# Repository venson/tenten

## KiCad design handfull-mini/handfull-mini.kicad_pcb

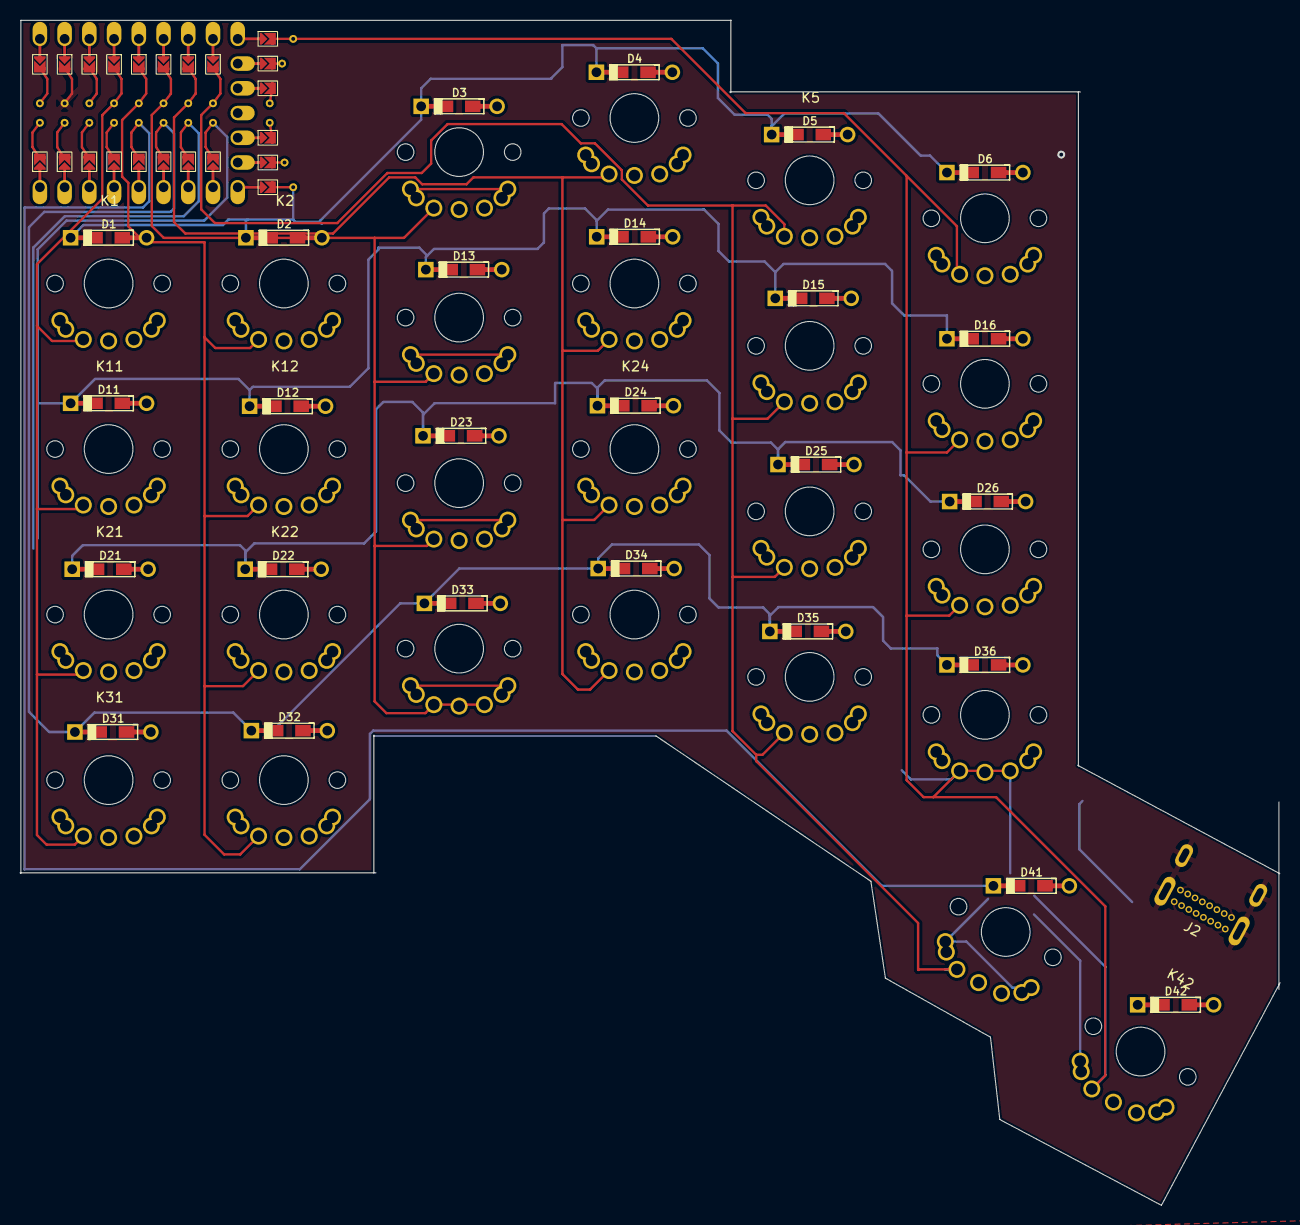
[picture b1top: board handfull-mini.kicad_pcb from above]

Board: 2 copper layers, 129.4 x 121.7 mm, 54 parts (0 on the bottom side), 39 nets.

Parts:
D1, D2, D3, D4, D5, D6, D11, D12, D13, D14, D15, D16, D21, D22, D23, D24, D25, D26, D31, D32, D33, D34, D35, D36, D41, D42: 1N4148; Diode-dual
J2: USB_C_Receptacle_USB2.0; USB_C_16p
K1, K2, K3, K4, K5, K6, K11, K12, K13, K14, K15, K16, K21, K22, K23, K24, K25, K26, K31, K32, K33, K34, K35, K36, K41, K42: SW_Key; gateron-ks27-choc-v1-reversible
U1: rp2040-zero; rp2040-zero-reform

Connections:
unnamed: D1.2 (A), K1.2
unnamed: D2.2 (A), K2.2
unnamed: D3.2 (A), K3.2
unnamed: D4.2 (A), K4.2
unnamed: D5.2 (A), K5.2
unnamed: D6.2 (A), K6.2
unnamed: D11.2 (A), K11.2
unnamed: D12.2 (A), K12.2
unnamed: D13.2 (A), K13.2
unnamed: D14.2 (A), K14.2
unnamed: D15.2 (A), K15.2
unnamed: D16.2 (A), K16.2
unnamed: D21.2 (A), K21.2
unnamed: D22.2 (A), K22.2
unnamed: D23.2 (A), K23.2
unnamed: D25.2 (A), K25.2
unnamed: D26.2 (A), K26.2
unnamed: D31.2 (A), K31.2
unnamed: D32.2 (A), K32.2
unnamed: D33.2 (A), K33.2
unnamed: D34.2 (A), K34.2
unnamed: D35.2 (A), K35.2
unnamed: D41.2 (A), K41.2
unnamed: D42.2 (A), K42.2
col0: K1.1, K11.1, K21.1, K31.1, U1.20 (29)
col1: K2.1, K12.1, K22.1, K32.1, U1.19 (28)
col2: K3.1, K13.1, K23.1, K33.1, U1.18 (27)
col3: K4.1, K14.1, K24.1, K34.1, U1.17 (26)
col4: K5.1, K15.1, K25.1, K35.1, K41.1, U1.16 (15)
col5: K6.1, K16.1, K26.1, K36.1, K42.1, U1.15 (14)
dataR: J2.A6 (D+), J2.B6 (D+), U1.2 (1)
dataT: J2.A7 (D-), J2.B7 (D-), U1.1 (0)
gnd: J2.A1 (GND), J2.A12 (GND), J2.B1 (GND), J2.B12 (GND), J2.S1 (SHIELD), U1.22 (GND)
row0: D1.1 (K), D2.1 (K), D3.1 (K), D4.1 (K), D5.1 (K), D6.1 (K), U1.9 (8)
row1: D11.1 (K), D12.1 (K), D13.1 (K), D14.1 (K), D15.1 (K), D16.1 (K), U1.8 (7)
row2: D21.1 (K), D22.1 (K), D23.1 (K), D24.1 (K), D25.1 (K), D26.1 (K), U1.7 (6)
row3: D31.1 (K), D32.1 (K), D33.1 (K), D34.1 (K), D35.1 (K), D36.1 (K), U1.6 (5)
row4: D41.1 (K), D42.1 (K), U1.5 (4)
vcc: J2.A4 (VBUS), J2.A9 (VBUS), J2.B4 (VBUS), J2.B9 (VBUS), U1.21 (3V3)

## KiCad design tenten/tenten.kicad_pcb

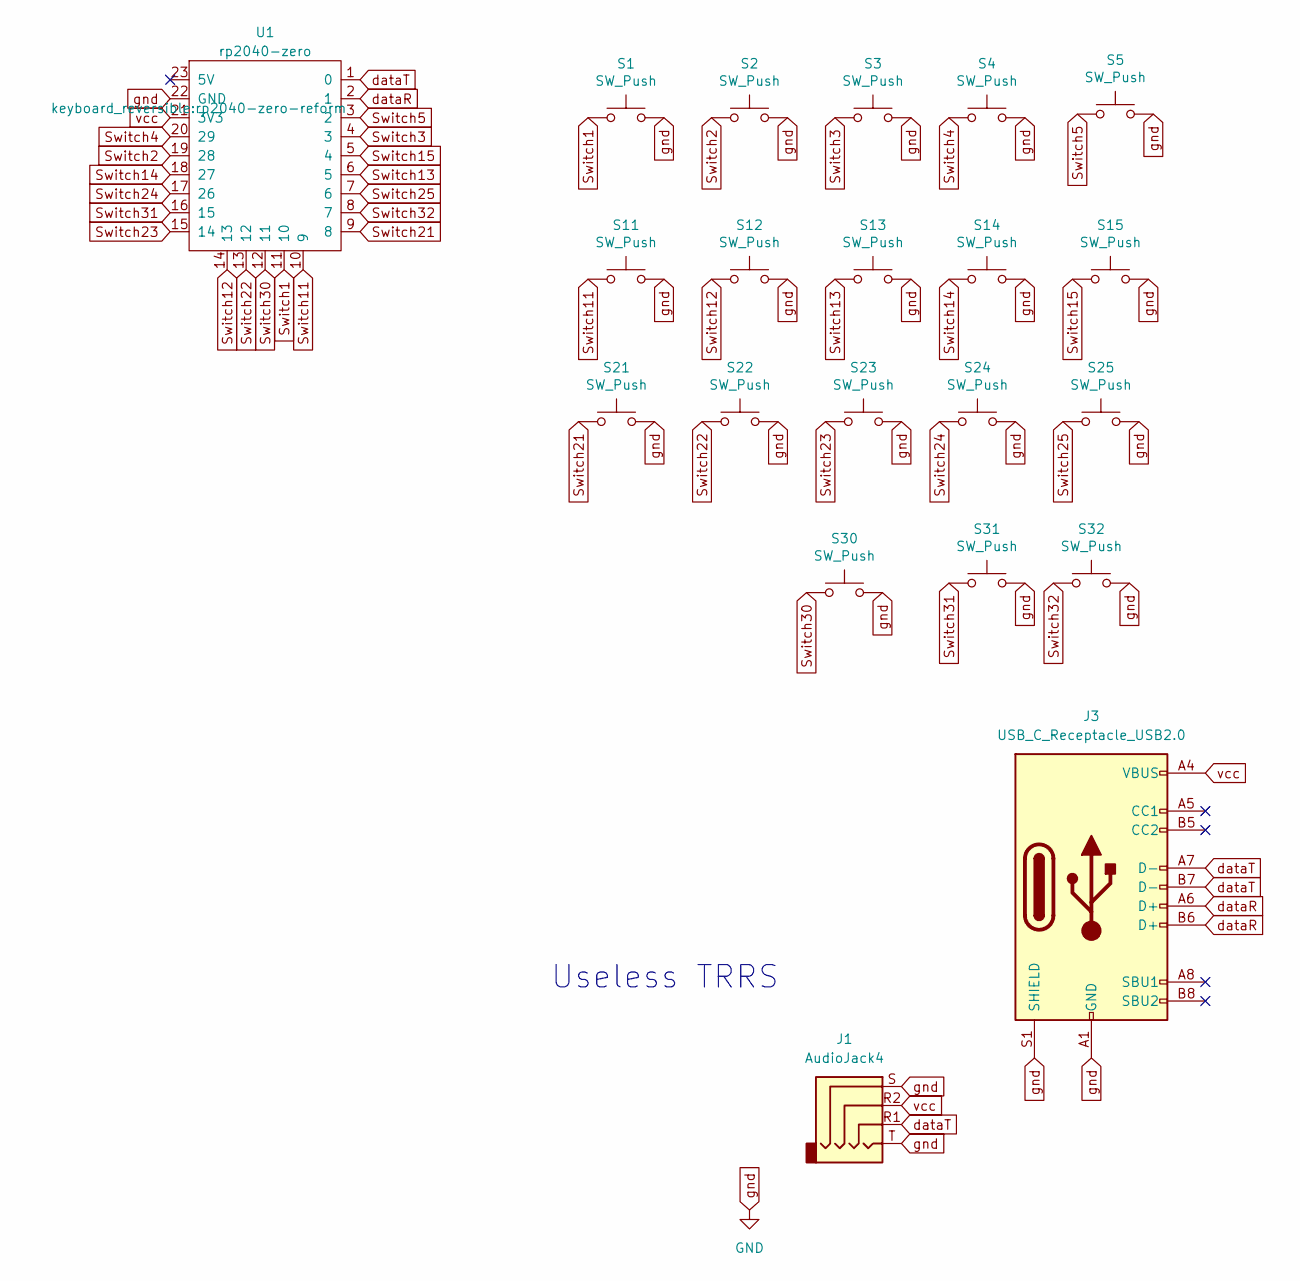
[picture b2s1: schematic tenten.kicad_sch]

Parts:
J1: AudioJack4; TRRS-PJ-320A
J3: USB_C_Receptacle_USB2.0; USB_C_16p
S1, S2, S3, S4, S5, S11, S12, S13, S14, S15, S21, S22, S23, S24, S25, S30, S31, S32: SW_Push; SW_PG1350_reversible_solder
U1: rp2040-zero; rp2040-zero-reform

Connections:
Switch1: S1.1, U1.11 (10)
Switch2: S2.1, U1.19 (28)
Switch3: S3.1, U1.4 (3)
Switch4: S4.1, U1.20 (29)
Switch5: S5.1, U1.3 (2)
Switch11: S11.1, U1.10 (9)
Switch12: S12.1, U1.14 (13)
Switch13: S13.1, U1.6 (5)
Switch14: S14.1, U1.18 (27)
Switch15: S15.1, U1.5 (4)
Switch21: S21.1, U1.9 (8)
Switch22: S22.1, U1.13 (12)
Switch23: S23.1, U1.15 (14)
Switch24: S24.1, U1.17 (26)
Switch25: S25.1, U1.7 (6)
Switch30: S30.1, U1.12 (11)
Switch31: S31.1, U1.16 (15)
Switch32: S32.1, U1.8 (7)
dataR: J3.A6 (D+), J3.B6 (D+), U1.2 (1)
dataT: J1.R1, J3.A7 (D-), J3.B7 (D-), U1.1 (0)
gnd: J1.S, J1.T, J3.A1 (GND), J3.A12 (GND), J3.B1 (GND), J3.B12 (GND), J3.S1 (SHIELD), S1.2, S2.2, S3.2, S4.2, S5.2, S11.2, S12.2, S13.2, S14.2, S15.2, S21.2, S22.2, S23.2, S24.2, S25.2, S30.2, S31.2, S32.2, U1.22 (GND)
vcc: J1.R2, J3.A4 (VBUS), J3.A9 (VBUS), J3.B4 (VBUS), J3.B9 (VBUS), U1.21 (3V3)

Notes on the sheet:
Useless TRRS

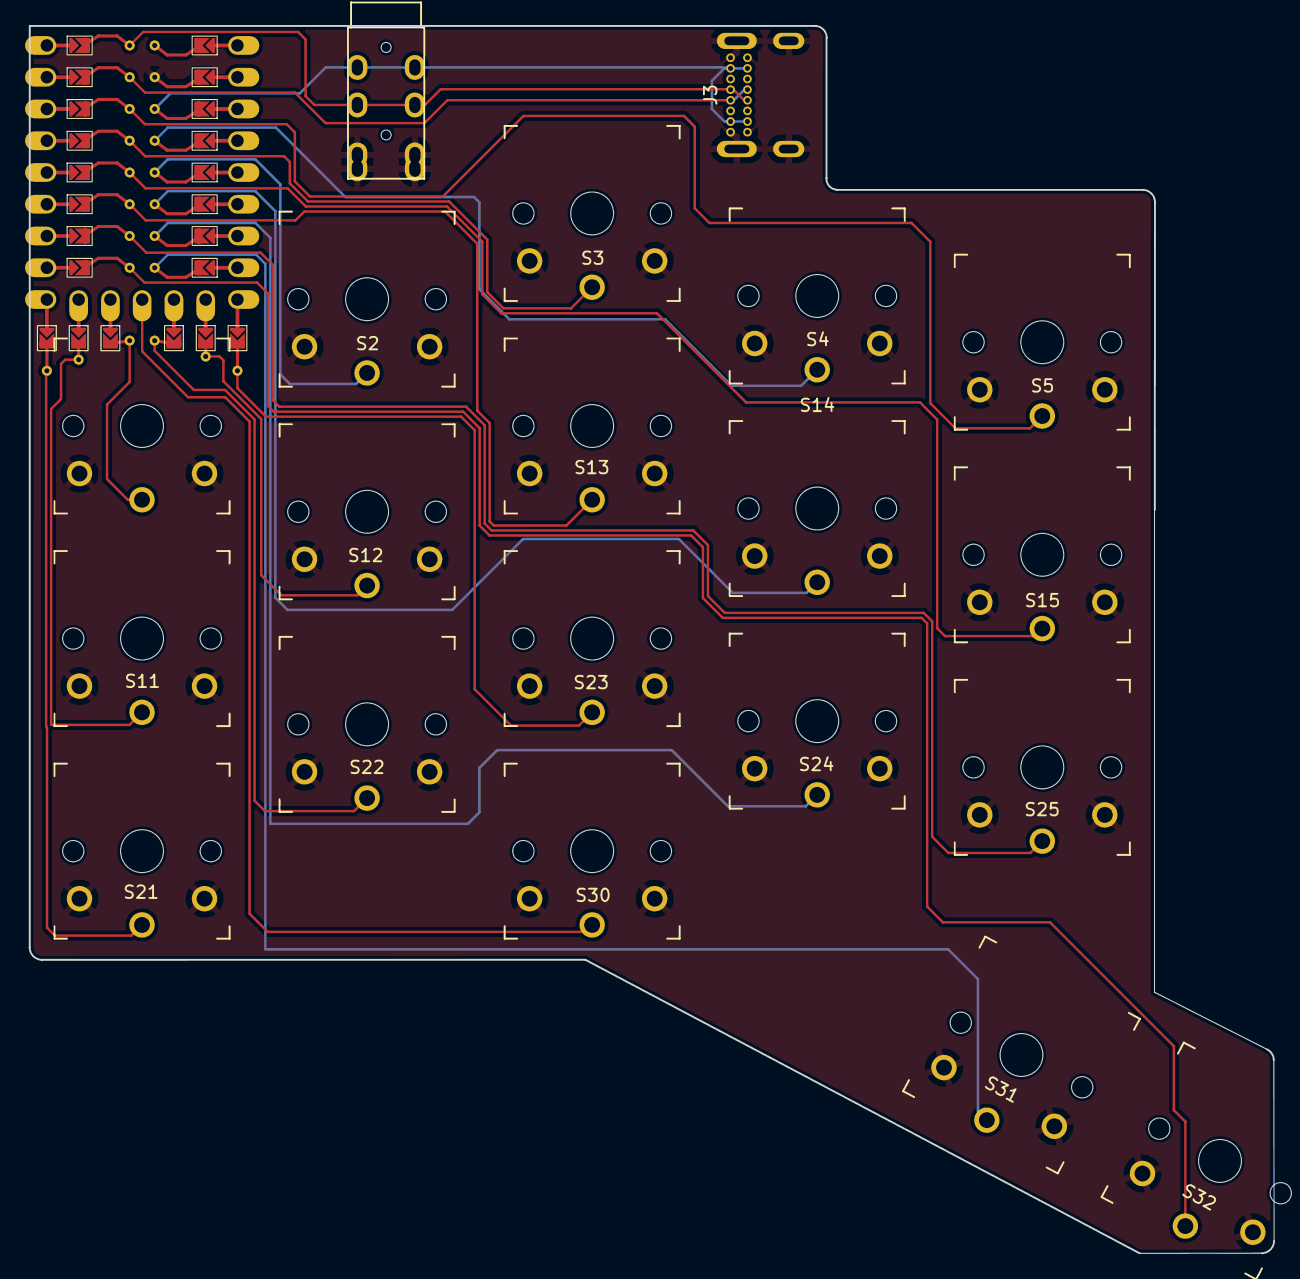
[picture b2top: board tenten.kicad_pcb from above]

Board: 2 copper layers, 99.5 x 98.2 mm, 21 parts (0 on the bottom side), 22 nets.

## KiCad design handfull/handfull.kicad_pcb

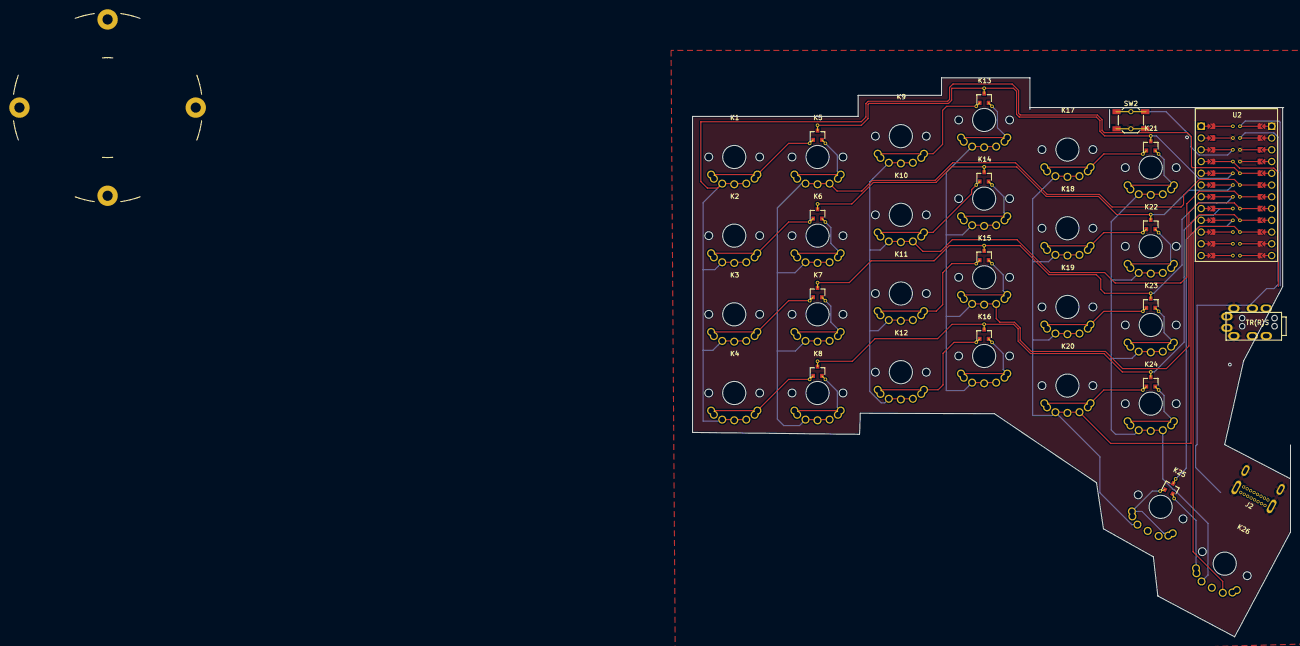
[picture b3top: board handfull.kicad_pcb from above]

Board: 2 copper layers, 129.2 x 120.8 mm, 44 parts (0 on the bottom side), 42 nets.

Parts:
D1, D2, D3, D4, D5, D6, D7, D8, D9, D10, D11, D12, D14: BAV70; SOT-23
H13: Mount_Tenting; Tenting_Puck
J2: USB_C_Receptacle_USB2.0; USB_C_16p
J5: TRRS; MJ-4PP-9
K1, K2, K3, K4, K5, K6, K7, K8, K9, K10, K11, K12, K13, K14, K15, K16, K17, K18, K19, K20, K21, K22, K23, K24, K25: SW_Key; gateron-ks27-choc-v1-reversible
K26: SW_Key; gateron-ks27-choc-v1-reversible-1.5
SW2: Reset; SW_SPST_SKQG_WithStem
U2: Elite-C; promicro-slim

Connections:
unnamed: D1.1 (A1), K1.2
unnamed: D1.2 (A2), K5.2
unnamed: D2.1 (A1), K2.2
unnamed: D2.2 (A2), K6.2
unnamed: D3.1 (A1), K3.2
unnamed: D3.2 (A2), K7.2
unnamed: D4.1 (A1), K4.2
unnamed: D4.2 (A2), K8.2
unnamed: D5.1 (A1), K12.2
unnamed: D5.2 (A2), K16.2
unnamed: D6.1 (A1), K9.2
unnamed: D6.2 (A2), K13.2
unnamed: D7.1 (A1), K10.2
unnamed: D7.2 (A2), K14.2
unnamed: D8.1 (A1), K11.2
unnamed: D8.2 (A2), K15.2
unnamed: D9.1 (A1), K20.2
unnamed: D9.2 (A2), K24.2
unnamed: D10.1 (A1), K17.2
unnamed: D10.2 (A2), K21.2
unnamed: D11.1 (A1), K18.2
unnamed: D11.2 (A2), K22.2
unnamed: D12.1 (A1), K19.2
unnamed: D12.2 (A2), K23.2
unnamed: D14.1 (A1), K25.2
unnamed: D14.2 (A2), K26.2
col0: K1.1, K2.1, K3.1, K4.1, U2.5 (2/PD1)
col1: K5.1, K6.1, K7.1, K8.1, U2.6 (3/PD0)
col2: K9.1, K10.1, K11.1, K12.1, U2.7 (4/PD4)
col3: K13.1, K14.1, K15.1, K16.1, U2.8 (5/PC6)
col4: K17.1, K18.1, K19.1, K20.1, K25.1, U2.9 (6/PD7)
col5: K21.1, K22.1, K23.1, K24.1, K26.1, U2.10 (7/PE6)
dataR: J2.A6 (D+), J2.B6 (D+), U2.2 (RX1/PD2)
dataT: J2.A7 (D-), J2.B7 (D-), J5.R1 (Ring1), U2.1 (TX0/PD3)
gnd: J2.A1 (GND), J2.A12 (GND), J2.B1 (GND), J2.B12 (GND), J2.S1 (SHIELD), J5.S (Sleeve), J5.T (Tip), SW2.2, U2.3 (GND), U2.4 (GND), U2.23 (GND)
reset: SW2.1, U2.22 (RST)
row0: D1.3 (K), D6.3 (K), D10.3 (K), U2.20 (A3/PF4)
row1: D2.3 (K), D7.3 (K), D11.3 (K), U2.19 (A2/PF5)
row2: D3.3 (K), D8.3 (K), D12.3 (K), U2.18 (A1/PF6)
row3: D4.3 (K), D5.3 (K), D9.3 (K), U2.17 (A0/PF7)
row4: D14.3 (K), U2.16 (15/PB1)
vcc: J2.A4 (VBUS), J2.A9 (VBUS), J2.B4 (VBUS), J2.B9 (VBUS), J5.R2 (Ring2), U2.21 (VCC)

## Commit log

2023-11-24 add sub project
